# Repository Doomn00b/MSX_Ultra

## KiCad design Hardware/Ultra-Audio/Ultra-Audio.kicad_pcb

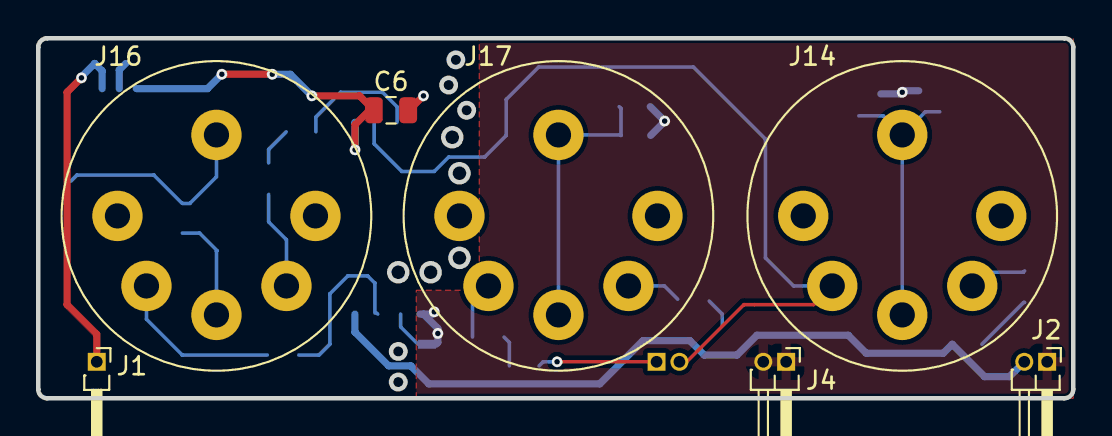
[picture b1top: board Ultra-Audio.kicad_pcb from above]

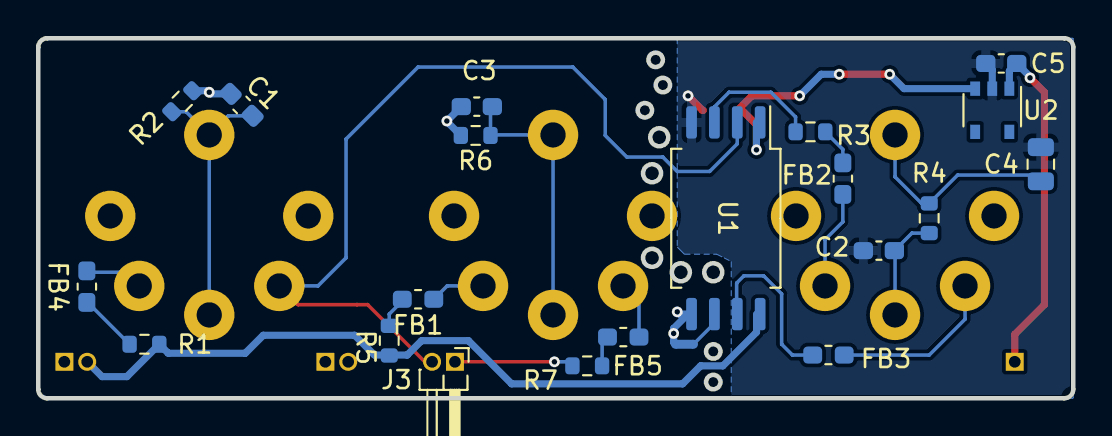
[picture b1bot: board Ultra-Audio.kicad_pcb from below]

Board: 2 copper layers, 57.5 x 20.0 mm, 28 parts (21 on the bottom side), 23 nets.

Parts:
C1, C2, C3, C5: C_CL10B104KB8NNNL; C_0603_1608Metric_Pad1.08x0.95mm_HandSolder
C4, C6: C_CL21B103KBANNNC; C_0805_2012Metric
FB1, FB2, FB3, FB4, FB5: L_ferrite_BLM18KG102SZ1D; L_0603_1608Metric_Pad1.05x0.95mm_HandSolder
J1: Conn_01x01; PinHeader_1x01_P1.27mm_Horizontal
J2, J3, J4: Conn_01x02; PinHeader_1x02_P1.27mm_Horizontal
J14, J16, J17: CUI_SD-50BV; Jack_DIN_CUI_SD-50BV_Vertical
R1, R3, R5, R7: R_CRGP0603F220R; R_0603_1608Metric
R2, R4, R6: R_ERJ-3GEYJ105V; R_0603_1608Metric
TP1: TestPoint_2Pole; NetTie-2_SMD_Pad0.5mm
U1: ADuM226; SOIC-8_7.5x5.85mm_P1.27mm
U2: AP7370; DIODES_SOT-753_SC-74A

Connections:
+5V: J2.2, R1.1, R5.1, U1.8 (VDD2)
+5VD: C6.1, U1.1 (VDD1), U2.3 (VOUT)
+12V: C5.1, J1.1, U2.1 (VIN)
/CSINKi: FB3.1, U1.7 (VIA)
/CSINKo: FB1.2, R5.2
/CSRCi: R3.1, U1.3 (VIB)
/CSRCo: FB5.1, R7.2
/MID_RX: J3.2, J14.5, U1.2 (VOA)
/MID_TX: J3.1, R7.1
Earth: C2.2, C4.2, C5.2, C6.2, U1.4 (GND1), U2.2 (GND)
GND: C1.2, C3.2, J2.1, J4.1, J4.2, R2.1, R6.1, TP1.1, U1.5 (GND2)
unnamed: C1.1, J14.2, J14.G, R2.2
unnamed: C2.1, J16.2, R4.1
unnamed: C3.1, J17.2, J17.G, R6.2
unnamed: C4.1, J16.G, R4.2
unnamed: FB1.1, J17.4
unnamed: FB2.1, J16.4
unnamed: FB2.2, R3.2
unnamed: FB3.2, J16.5
unnamed: FB4.1, J14.4
unnamed: FB4.2, R1.2
unnamed: FB5.2, J17.5
unnamed: TP1.2, U1.6 (VOB)

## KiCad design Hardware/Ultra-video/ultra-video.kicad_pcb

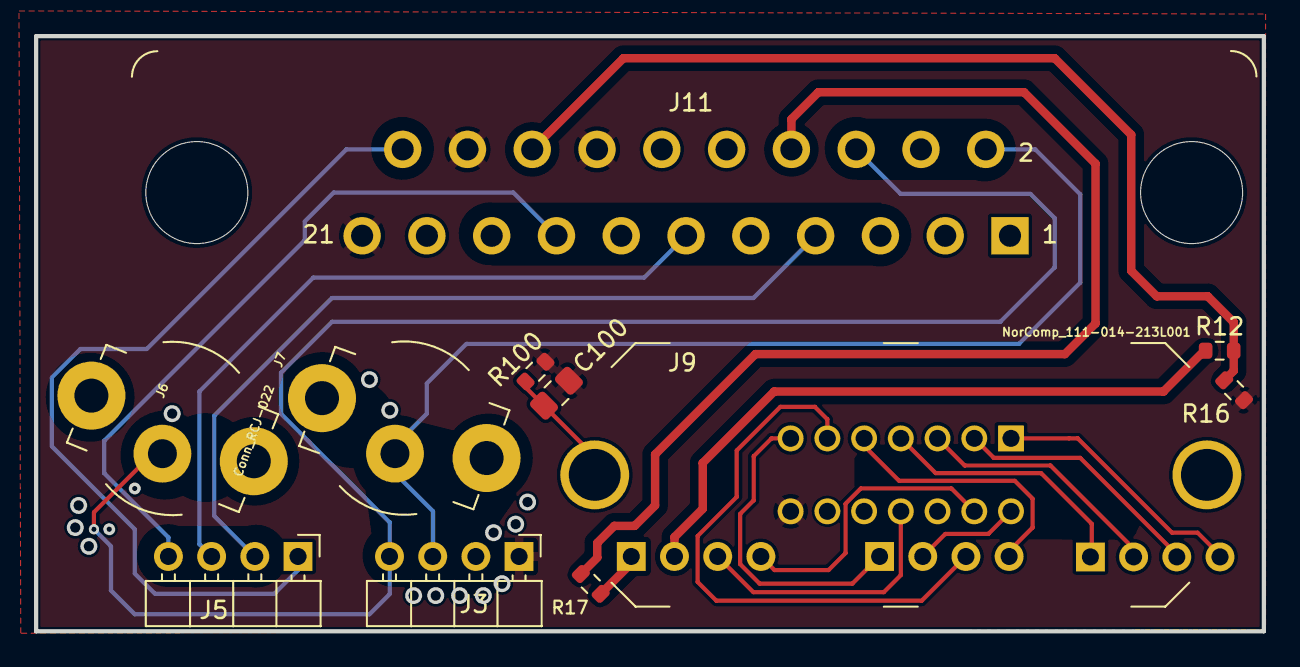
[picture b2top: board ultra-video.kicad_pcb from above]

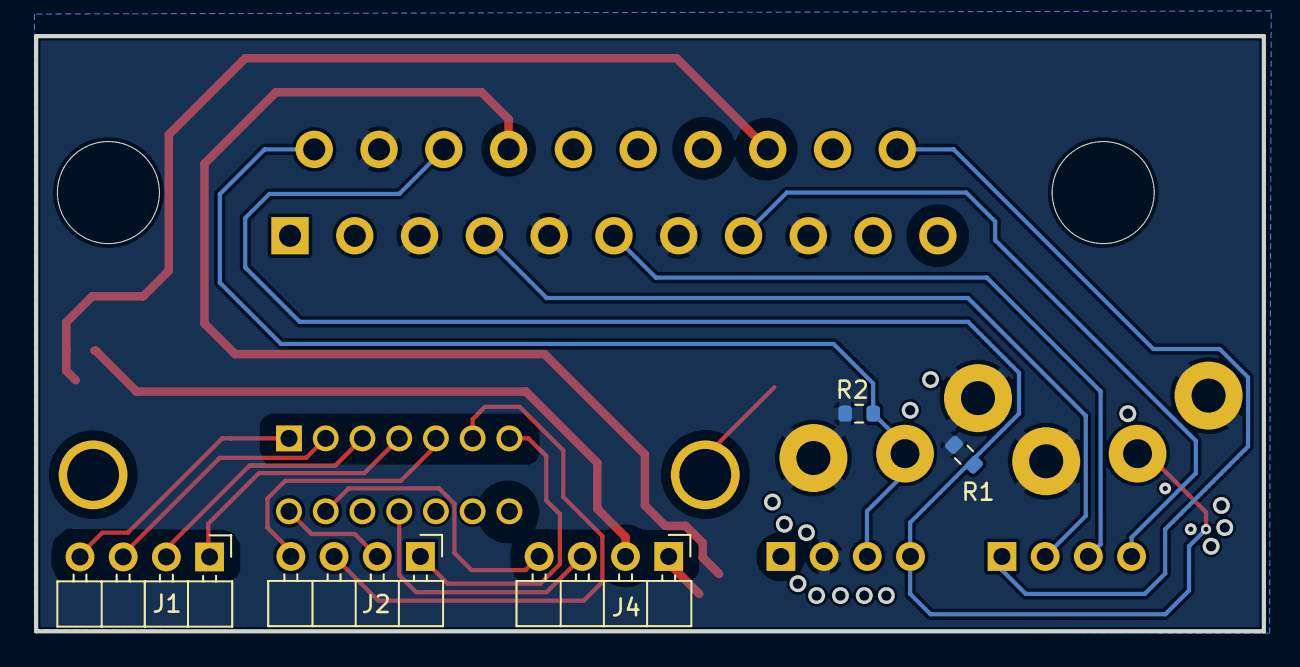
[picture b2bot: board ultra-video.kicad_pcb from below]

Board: 2 copper layers, 72.2 x 35.0 mm, 16 parts (5 on the bottom side), 23 nets.

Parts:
C100: C_CL21B105KBFNNNF; C_0805_2012Metric_Pad1.18x1.45mm_HandSolder
J1, J2, J3, J4, J5: Conn_01x04; PinHeader_1x04_P2.54mm_Horizontal_less-silk
J6: Conn_RCJ-023; CUI_RCJ-023
J7: Conn_RCJ-022; CUI_RCJ-022
J9: NorComp_111-014-213L001; Conn_Micro_Ribbon_14F_Vertical
J11: TC_1578891_SCART; SCART-21_Female_Vertical_P1.905x2.54mm_EdgePinOffset10.7mm
R1, R2: 47k; R_0603_1608Metric
R12, R16: 100; R_0603_1608Metric
R17: 1k; R_0603_1608Metric
R100: R_ERJ-3GEYJ105V; R_0603_1608Metric

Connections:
+5V: J4.2, R12.1
+12V: J4.1, R17.2
/2.5V: J11.16 (BLNK), R12.2, R16.1
/+12V-1K: J11.8 (SW), R17.1
/AUD_L: J3.4, J6.2 (IN2), J11.6 (AIL/MONO), R1.1
/AUD_R: J3.3, J7.2 (IN2), J11.2 (AIR), R2.2
/BOUT: J5.2, J11.7 (BLUE)
/CSYNC: J5.1, J11.20 (VIDIN/Sync)
/GOUT: J5.3, J11.11 (GREEN)
/PD0: J1.3, J9.2
/PD1: J1.2, J9.3
/PD2: J1.1, J9.4
/PD3: J2.4, J9.5
/PD4: J2.3, J9.6
/PD5: J2.1, J9.7
/PD6: J2.2, J9.8
/PD7: J4.4, J9.9
/PRT_BUSY: J4.3, J9.11
/ROUT: J5.4, J11.15 (RED/CHROMA)
/~STROBE: J1.4, J9.1
GND: C100.2, J3.1, J9.14, J11.14 (DATGND), J11.18 (BLNKGND), J11.21 (SH), R16.2, R100.1
GNDA: J3.2, J6.1A (IN1), J6.1B (IN1), J7.1A (IN1), J7.1B (IN1), J11.4 (AUGND), J11.5 (BGND), J11.9 (GGND), J11.13 (RGND), J11.17 (VGND), R1.2, R2.1
unnamed: C100.1, J9.15 (SH), R100.2

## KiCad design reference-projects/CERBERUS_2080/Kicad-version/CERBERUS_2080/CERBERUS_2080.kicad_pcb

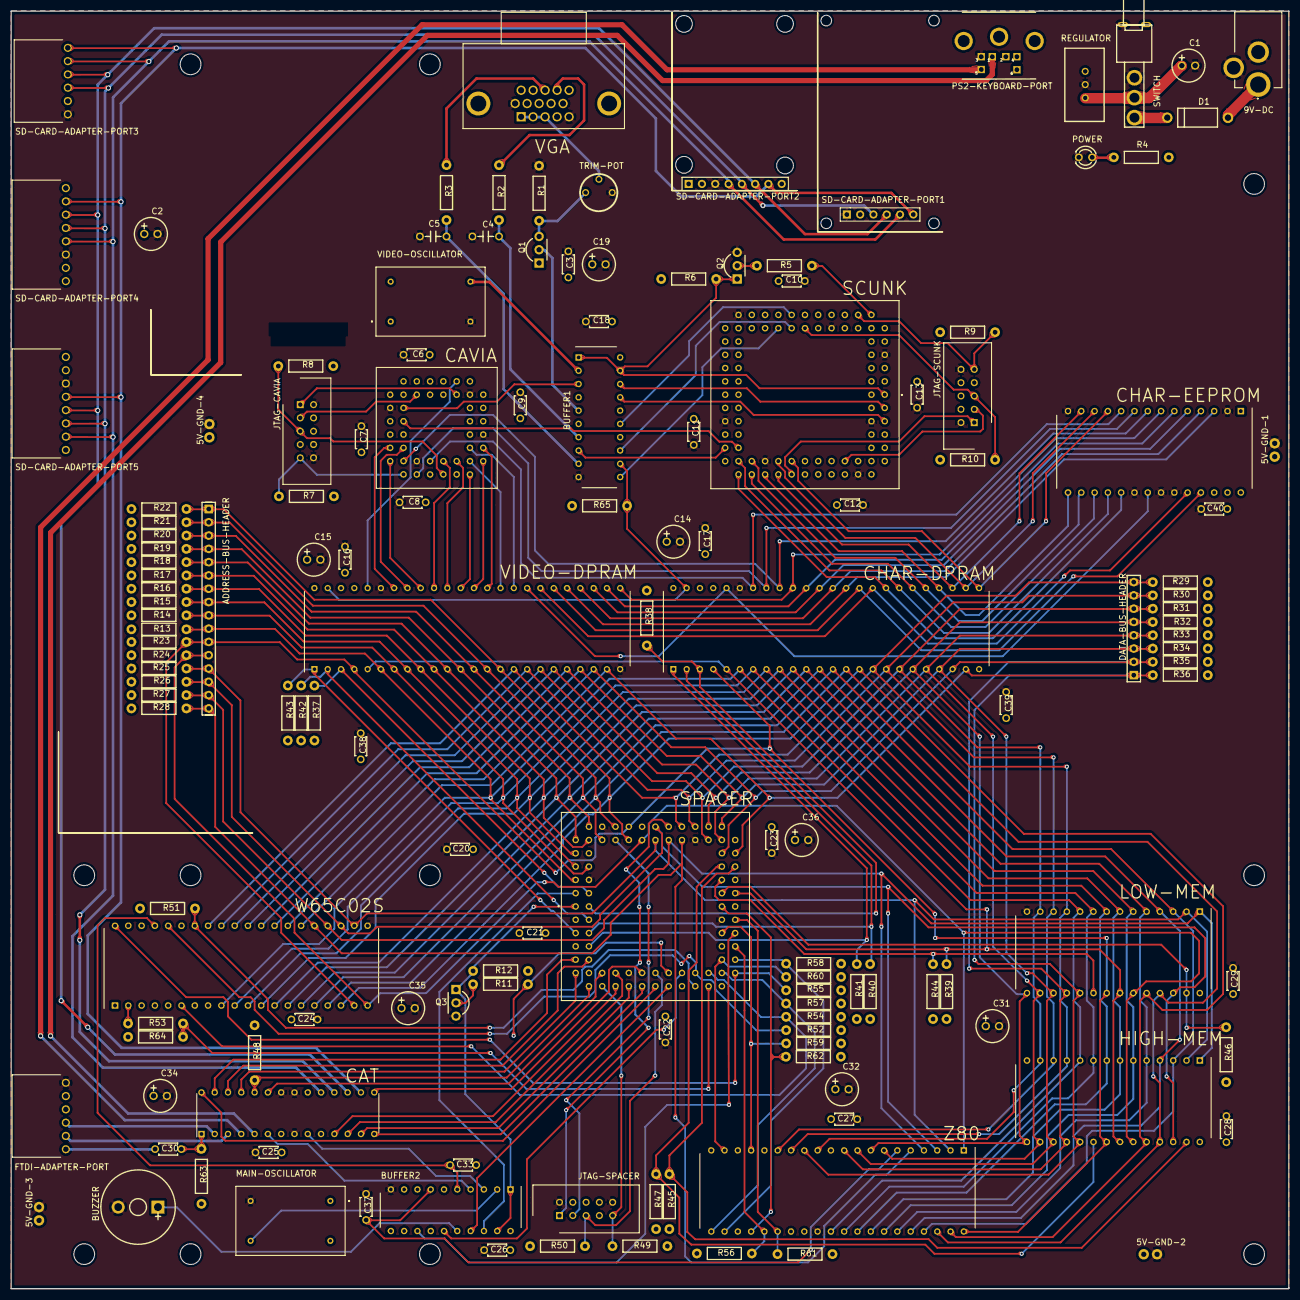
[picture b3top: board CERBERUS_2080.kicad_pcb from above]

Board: 2 copper layers, 244.1 x 244.1 mm, 147 parts (0 on the bottom side), 150 nets.

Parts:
5V-GND-1, 5V-GND-2, 5V-GND-3, 5V-GND-4: Pin Header, VERT, TH, 2.54mm; HDR-TH_2P-P2.54-V-R1-C2-D1.0
9V-DC: Wurth-Elektronik-694106301002; KLDX0202APLT
ADDRESS-BUS-HEADER: P125-1116A0BS116AX; H16-2.54
BUFFER1, BUFFER2: SN74HC244N; DIP794W53P254L2540H508Q20N
BUZZER: Ekulit RMP-14SP; BUZZER-R14-2P-7.6PITCH
C1: 470µF; CAP-TH_BD6.3-P2.50-D1.0-FD
C2, C19, C31, C35: 10µF; CAP-TH_BD6.3-P2.50-D1.0-FD
C3, C6, C7, C8, C9, C10, C11, C12, C13, C16, C17, C18, C20, C21, C22, C23, C24, C25, C26, C27, C28, C29, C30, C38, C39, C40: 100nF; CAP-TH_L3.6-W2.3-P5.00-D0.5
C4, C5: 470pF; CAP-TH_L5.0-W2.5-P5.08-D0.7
C14, C15, C32, C34, C36: 100µF; CAP-TH_BD6.3-P2.50-D1.0-FD
C33, C37: 100pF; CAP-TH_L3.6-W2.3-P5.00-D0.5
CAT: ATMEGA328P-PU; DIP794W53P254L3467H457Q28N
CAVIA: ATF1504AS; PLCC-44
CHAR-DPRAM: 7132LA55PDGI; DIP1549W51P254L6185H508Q48N
CHAR-EEPROM: AT28C64B-15PU; DIP1556W56P254L3702H483Q28N
D1: SB2H100-E3/54; DO-15_BD3.1-L6.7-P10.70-D0.9-RD
DATA-BUS-HEADER: F185-1108A1BSYC1; H8-2.54
FTDI-ADAPTER-PORT: SSW-106-02-F-S-RA; SSW-106-XX-YYY-S-RA
HIGH-MEM: AS6C62256-55PCN; DIP1556W56P254L3702H483Q28N
JTAG-CAVIA: 103308-1; SHDR10W66P254_2X5_2032X914X978
JTAG-SCUNK: 103308-1; SHDR10W66P254_2X5_2032X914X978
JTAG-SPACER: 103308-1; SHDR10W66P254_2X5_2032X914X978
LOW-MEM: AS6C62256-55PCN; DIP1556W56P254L3702H483Q28N
MAIN-OSCILLATOR: OSZI 16,000000; ECS100AX240
POWER: Wurth-Elektronik-151051BS04000; LED-TH_BD3.0-P2.54-FD
PS2-KEYBOARD-PORT: CADANIA 1AA300833_JHJC; PS2_PORT
Q1: BC337-40; TO-92-3_L4.8-W3.7-P2.54-L
Q2, Q3: BC547B; TO-92-3_L4.8-W3.7-P2.54-L
R1, R4: 220Ω; RES-TH_BD2.3-L6.5-P10.50-D0.5
R2, R3: 68Ω; RES-TH_BD2.3-L6.5-P10.50-D0.5
R5, R6, R7, R8, R9, R10, R11, R12, R13, R14, R15, R16, R17, R18, R19, R20, R21, R22, R23, R24, R25, R26, R27, R28, R29, R30, R31, R32, R33, R34, R35, R36, R39, R40, R41, R42, R43, R44, R45, R46, R47, R48, R49, R50, R51, R52, R54, R55, R56, R57, R58, R59, R60, R61, R62, R63, R64, R65: 10KΩ; RES-TH_BD2.3-L6.5-P10.50-D0.5
R37, R38: 270Ω; RES-TH_BD2.3-L6.5-P10.50-D0.5
R53: 2K2Ω; RES-TH_BD2.3-L6.5-P10.50-D0.5
REGULATOR: TSR_2-2450; TSR-2
SCUNK: ATF1508AS; 5408808424008
SD-CARD-ADAPTER-PORT1: MOLEX 90147-1106; HDR-F-2.54_1X6
SD-CARD-ADAPTER-PORT2: MOLEX 90147-1108; HDR-F-2.54_1X8
SD-CARD-ADAPTER-PORT3: SSW-106-02-F-S-RA; SSW-106-XX-YYY-S-RA
SD-CARD-ADAPTER-PORT4, SD-CARD-ADAPTER-PORT5: SSW-108-02-G-S-RA; SSW-108-XX-YYY-S-RA
SPACER: ATF1508AS; 5408808424008
SWITCH: 500SSP1S2M7QEA; SW-TH_500SSP1S2M7QEA
TRIM-POT: T7YA103MT20; T7YA
VGA: L77HDE15SD1CH4RHNVGA
VIDEO-DPRAM: 7132LA55PDGI; DIP1549W51P254L6185H508Q48N
VIDEO-OSCILLATOR: ECS-100AX-25.175; ECS100AX240
W65C02S: W65C02S6TPG-14; DIP1524W56P254L5207H508Q40N
Z80: Z84C0010PEG; DIP1550W53P254L5232H424Q40N

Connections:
9V-DC_1: 9V-DC.1, D1.2
A0: ADDRESS-BUS-HEADER.10, CHAR-DPRAM.6, HIGH-MEM.10, LOW-MEM.10, R13.2, SPACER.81, VIDEO-DPRAM.6, W65C02S.9, Z80.30
A1: ADDRESS-BUS-HEADER.9, CHAR-DPRAM.7, HIGH-MEM.9, LOW-MEM.9, R14.2, SPACER.80, VIDEO-DPRAM.7, W65C02S.10, Z80.31
A2: ADDRESS-BUS-HEADER.8, CHAR-DPRAM.8, HIGH-MEM.8, LOW-MEM.8, R15.2, SPACER.79, VIDEO-DPRAM.8, W65C02S.11, Z80.32
A3: ADDRESS-BUS-HEADER.7, CHAR-DPRAM.9, HIGH-MEM.7, LOW-MEM.7, R16.2, SPACER.77, VIDEO-DPRAM.9, W65C02S.12, Z80.33
A4: ADDRESS-BUS-HEADER.6, CHAR-DPRAM.10, HIGH-MEM.6, LOW-MEM.6, R17.2, SPACER.76, VIDEO-DPRAM.10, W65C02S.13, Z80.34
A5: ADDRESS-BUS-HEADER.5, CHAR-DPRAM.11, HIGH-MEM.5, LOW-MEM.5, R18.2, SPACER.75, VIDEO-DPRAM.11, W65C02S.14, Z80.35
A6: ADDRESS-BUS-HEADER.4, CHAR-DPRAM.12, HIGH-MEM.4, LOW-MEM.4, R19.2, SPACER.74, VIDEO-DPRAM.12, W65C02S.15, Z80.36
A7: ADDRESS-BUS-HEADER.3, CHAR-DPRAM.13, HIGH-MEM.3, LOW-MEM.3, R20.2, SPACER.73, VIDEO-DPRAM.13, W65C02S.16, Z80.37
A8: ADDRESS-BUS-HEADER.2, CHAR-DPRAM.14, HIGH-MEM.25, LOW-MEM.25, R21.2, SPACER.70, VIDEO-DPRAM.14, W65C02S.17, Z80.38
A9: ADDRESS-BUS-HEADER.1, CHAR-DPRAM.15, HIGH-MEM.24, LOW-MEM.24, R22.2, SPACER.69, VIDEO-DPRAM.15, W65C02S.18, Z80.39
A10: ADDRESS-BUS-HEADER.11, CHAR-DPRAM.4, HIGH-MEM.21, LOW-MEM.21, R23.2, SPACER.68, VIDEO-DPRAM.4, W65C02S.19, Z80.40
A11: ADDRESS-BUS-HEADER.12, HIGH-MEM.23, LOW-MEM.23, R24.2, SPACER.67, W65C02S.20, Z80.1
A12: ADDRESS-BUS-HEADER.13, HIGH-MEM.2, LOW-MEM.2, R25.2, SPACER.65, W65C02S.22, Z80.2
A13: ADDRESS-BUS-HEADER.14, HIGH-MEM.26, LOW-MEM.26, R26.2, SPACER.64, W65C02S.23, Z80.3
A14: ADDRESS-BUS-HEADER.15, HIGH-MEM.1, LOW-MEM.1, R27.2, SPACER.63, W65C02S.24, Z80.4
A15: ADDRESS-BUS-HEADER.16, R28.2, SPACER.61, W65C02S.25, Z80.5
AOE: CAT.25, SPACER.11
BCATCLK: BUFFER2.3, CAT.9
BCCLK: BUFFER1.3, CAVIA.43
BCLK6502: BUFFER2.5, C33.2, W65C02S.37
BCLKZ80: BUFFER2.7, C37.2, Z80.6
BDPMCE: BUFFER1.12, CHAR-DPRAM.47, R65.1, VIDEO-DPRAM.47
BE6502: R52.2, SPACER.29, W65C02S.36
BMCLK: BUFFER2.18, SPACER.83
BPCLK: BUFFER1.18, SCUNK.83
BSOUND: BUFFER2.16, BUZZER.1
BUFFER1_5: BUFFER1.5, Q1.2
BUFFER1_7: BUFFER1.7, C4.1, R2.1
BUFFER1_9: BUFFER1.9, C5.1, R3.1
BUSREQZ80: R56.2, SPACER.37, Z80.25
C1_1: C1.1, REGULATOR.1, SWITCH.2
C-TCK: CAVIA.32, JTAG-CAVIA.1
C-TDI: CAVIA.7, JTAG-CAVIA.9, R7.1
C-TDO: CAVIA.38, JTAG-CAVIA.3
C-TMS: CAVIA.13, JTAG-CAVIA.5, R8.1
CATCLK: BUFFER2.17, SPACER.24
CATEXTRA: CAT.15, SPACER.21
CATRST: C30.1, FTDI-ADAPTER-PORT.6
CAT_1: C30.2, CAT.1, R63.2
CB0: CHAR-DPRAM.25, CHAR-EEPROM.11, SCUNK.63
CB1: CHAR-DPRAM.26, CHAR-EEPROM.12, SCUNK.61
CB2: CHAR-DPRAM.27, CHAR-EEPROM.13, SCUNK.60
CB3: CHAR-DPRAM.28, CHAR-EEPROM.15, SCUNK.58
CB4: CHAR-DPRAM.29, CHAR-EEPROM.16, SCUNK.57
CB5: CHAR-DPRAM.30, CHAR-EEPROM.17, SCUNK.56
CB6: CHAR-DPRAM.31, CHAR-EEPROM.18, SCUNK.55
CB7: CHAR-DPRAM.32, CHAR-EEPROM.19, SCUNK.54
CBUSY: CHAR-DPRAM.3, R38.2, SPACER.2
CCLK: BUFFER1.17, SCUNK.81
CECM: CHAR-DPRAM.1, R41.2, SPACER.8
CEHM: HIGH-MEM.20, R47.2, SPACER.50
CELM: LOW-MEM.20, R44.2, SPACER.48
CEVM: R43.2, SPACER.5, VIDEO-DPRAM.1
CLK6502: BUFFER2.15, SPACER.27
CLKZ80: BUFFER2.13, SPACER.39
CMA0: CAVIA.12, CHAR-DPRAM.42, CHAR-EEPROM.10
CMA1: CAVIA.9, CHAR-DPRAM.41, CHAR-EEPROM.9
CMA2: CAVIA.8, CHAR-DPRAM.40, CHAR-EEPROM.8
CMA3: CHAR-DPRAM.39, CHAR-EEPROM.7, VIDEO-DPRAM.25
CMA4: CHAR-DPRAM.38, CHAR-EEPROM.6, VIDEO-DPRAM.26
CMA5: CHAR-DPRAM.37, CHAR-EEPROM.5, VIDEO-DPRAM.27
CMA6: CHAR-DPRAM.36, CHAR-EEPROM.4, VIDEO-DPRAM.28
CMA7: CHAR-DPRAM.35, CHAR-EEPROM.3, VIDEO-DPRAM.29
CMA8: CHAR-DPRAM.34, CHAR-EEPROM.25, VIDEO-DPRAM.30
CMA9: CHAR-DPRAM.33, CHAR-EEPROM.24, VIDEO-DPRAM.31
CMA10: CHAR-DPRAM.44, CHAR-EEPROM.21, VIDEO-DPRAM.32
CPUGO: CAT.13, SPACER.18
CPUIRQ: CAT.12, SPACER.17
CPURST: CAT.14, SPACER.20
CPUSLC: CAT.11, SPACER.16
CRST: CAVIA.1, SCUNK.52
CS: CAT.16, SD-CARD-ADAPTER-PORT1.6, SD-CARD-ADAPTER-PORT2.7, SD-CARD-ADAPTER-PORT3.1, SD-CARD-ADAPTER-PORT4.2, SD-CARD-ADAPTER-PORT5.4
D0: CHAR-DPRAM.16, DATA-BUS-HEADER.8, HIGH-MEM.11, LOW-MEM.11, R29.2, SPACER.60, VIDEO-DPRAM.16, W65C02S.33, Z80.14
D1: CHAR-DPRAM.17, DATA-BUS-HEADER.7, HIGH-MEM.12, LOW-MEM.12, R30.2, SPACER.58, VIDEO-DPRAM.17, W65C02S.32, Z80.15
D1_1: D1.1, SWITCH.3
D2: CHAR-DPRAM.18, DATA-BUS-HEADER.6, HIGH-MEM.13, LOW-MEM.13, R31.2, SPACER.57, VIDEO-DPRAM.18, W65C02S.31, Z80.12
D3: CHAR-DPRAM.19, DATA-BUS-HEADER.5, HIGH-MEM.15, LOW-MEM.15, R32.2, SPACER.56, VIDEO-DPRAM.19, W65C02S.30, Z80.8
D4: CHAR-DPRAM.20, DATA-BUS-HEADER.4, HIGH-MEM.16, LOW-MEM.16, R33.2, SPACER.55, VIDEO-DPRAM.20, W65C02S.29, Z80.7
D5: CHAR-DPRAM.21, DATA-BUS-HEADER.3, HIGH-MEM.17, LOW-MEM.17, R34.2, SPACER.54, VIDEO-DPRAM.21, W65C02S.28, Z80.9
D6: CHAR-DPRAM.22, DATA-BUS-HEADER.2, HIGH-MEM.18, LOW-MEM.18, R35.2, SPACER.52, VIDEO-DPRAM.22, W65C02S.27, Z80.10
D7: CHAR-DPRAM.23, DATA-BUS-HEADER.1, HIGH-MEM.19, LOW-MEM.19, R36.2, SPACER.51, VIDEO-DPRAM.23, W65C02S.26, Z80.13
DPMCE: BUFFER1.8, SCUNK.51
GND: 5V-GND-1.1, 5V-GND-2.1, 5V-GND-3.1, 5V-GND-4.1, 9V-DC.2, 9V-DC.3, BUFFER1.10, BUFFER2.10, BUZZER.2, C1.2, C2.2, C3.2, C4.2, C5.2, C6.2, C7.2, C8.2, C9.2, C10.2, C11.2, C12.2, C13.2, C14.2, C15.2, C16.2, C17.2, C18.2, C19.2, C20.2, C21.2, C22.2, C23.2, C24.2, C25.2, C26.2, C27.2, C28.2, C29.2, C31.2, C32.2, C33.1, C34.2, C35.2, C36.2, C37.1, C38.2, C39.2, C40.2, CAT.8, CAT.21, CAT.22, CAVIA.10, CAVIA.22, CAVIA.30, CAVIA.42, CHAR-DPRAM.24, CHAR-DPRAM.43, CHAR-EEPROM.2, CHAR-EEPROM.14, CHAR-EEPROM.20, CHAR-EEPROM.22, CHAR-EEPROM.23, FTDI-ADAPTER-PORT.1, HIGH-MEM.14, JTAG-CAVIA.2, JTAG-CAVIA.10, JTAG-SCUNK.2, JTAG-SCUNK.10, JTAG-SPACER.2, JTAG-SPACER.10, LOW-MEM.14, MAIN-OSCILLATOR.7, POWER.2, PS2-KEYBOARD-PORT.3, Q2.3, Q3.3, R1.1, REGULATOR.2, SCUNK.7, SCUNK.19, SCUNK.32, SCUNK.42, SCUNK.47, SCUNK.59, SCUNK.72, SCUNK.82, SD-CARD-ADAPTER-PORT1.1, SD-CARD-ADAPTER-PORT2.3, SD-CARD-ADAPTER-PORT3.6, SD-CARD-ADAPTER-PORT4.6, SD-CARD-ADAPTER-PORT5.3, SPACER.7, SPACER.19, SPACER.32, SPACER.42, SPACER.47, SPACER.59, SPACER.72, SPACER.82, SWITCH.1, SWITCH.5, TRIM-POT.C, VGA.5, VGA.6, VGA.7, VGA.8, VGA.10, VIDEO-DPRAM.24, VIDEO-DPRAM.43, VIDEO-OSCILLATOR.7, W65C02S.21, Z80.29
HSP: BUFFER1.11, SCUNK.27
KCLK: CAT.4, PS2-KEYBOARD-PORT.5
KDAT: CAT.5, PS2-KEYBOARD-PORT.1
LD: CAT.23, SPACER.15
MCLK: BUFFER2.2, MAIN-OSCILLATOR.8
MISO: CAT.18, SD-CARD-ADAPTER-PORT1.3, SD-CARD-ADAPTER-PORT2.5, SD-CARD-ADAPTER-PORT3.4, SD-CARD-ADAPTER-PORT4.4, SD-CARD-ADAPTER-PORT5.6
MOSI: CAT.17, SD-CARD-ADAPTER-PORT1.4, SD-CARD-ADAPTER-PORT2.6, SD-CARD-ADAPTER-PORT3.3, SD-CARD-ADAPTER-PORT4.3, SD-CARD-ADAPTER-PORT5.5
MREQZ80: R60.2, SPACER.36, Z80.19
NMIB6502: R54.2, SPACER.31, W65C02S.6
NMIZ80: R59.2, SPACER.40, Z80.17
OE: CHAR-DPRAM.5, HIGH-MEM.22, LOW-MEM.22, R39.2, SPACER.45, VIDEO-DPRAM.5
PCLK: BUFFER1.2, VIDEO-OSCILLATOR.8
POWER_1: POWER.1, R4.2
Q2_2: Q2.2, R5.1
R11_1: Q3.2, R11.1
RDY6502: R53.1, R64.2, SPACER.30
RDZ80: R57.2, SPACER.34, Z80.21
RGB: BUFFER1.15, SCUNK.24
RST6502: R55.2, SPACER.33, W65C02S.40
RSTZ80: R61.2, SPACER.41, Z80.26
RWB6502: R51.2, SPACER.28, W65C02S.34
RWCAT: CAT.24, R48.2, SPACER.12
RWCM: CHAR-DPRAM.2, R40.2, SPACER.6
RWVM: R42.2, SPACER.4, VIDEO-DPRAM.2
RX: CAT.2, FTDI-ADAPTER-PORT.4
S-TCK: JTAG-SCUNK.1, SCUNK.62
S-TDI: JTAG-SCUNK.9, R9.1, SCUNK.14
S-TDO: JTAG-SCUNK.3, SCUNK.71
S-TMS: JTAG-SCUNK.5, R10.1, SCUNK.23
SBE: R5.2, SCUNK.12
SC: CAT.26, SPACER.10
SCK: CAT.19, SD-CARD-ADAPTER-PORT1.5, SD-CARD-ADAPTER-PORT2.4, SD-CARD-ADAPTER-PORT3.2, SD-CARD-ADAPTER-PORT4.5, SD-CARD-ADAPTER-PORT5.7
SI: CAT.27, SPACER.9
SO: CAT.28, SPACER.22
SOUND: BUFFER2.4, CAT.6
SP-TCK: JTAG-SPACER.1, SPACER.62
SP-TDI: JTAG-SPACER.9, R49.1, SPACER.14
SP-TDO: JTAG-SPACER.3, SPACER.71
SP-TMS: JTAG-SPACER.5, R50.1, SPACER.23
SPBE: R11.2, SPACER.25
SPRST: BUFFER2.1, BUFFER2.19, Q3.1, R12.1, SPACER.1
SRST: BUFFER1.1, BUFFER1.19, Q2.1, R6.1, SCUNK.1
TRIM-POT_A: Q1.3, R1.2, TRIM-POT.A
TX: CAT.3, FTDI-ADAPTER-PORT.5
VBUSY: R37.2, SPACER.84, VIDEO-DPRAM.3
VCC: 5V-GND-1.2, 5V-GND-2.2, 5V-GND-3.2, 5V-GND-4.2, BUFFER1.20, BUFFER2.20, C2.1, C3.1, C6.1, C7.1, C8.1, C9.1, C10.1, C11.1, C12.1, C13.1, C14.1, C15.1, C16.1, C17.1, C18.1, C19.1, C20.1, C21.1, C22.1, C23.1, C24.1, C25.1, C26.1, C27.1, C28.1, C29.1, C31.1, C32.1, C34.1, C35.1, C36.1, C38.1, C39.1, C40.1, CAT.7, CAT.20, CAVIA.3, CAVIA.15, CAVIA.23, CAVIA.35, CHAR-DPRAM.46, CHAR-DPRAM.48, CHAR-EEPROM.27, CHAR-EEPROM.28, FTDI-ADAPTER-PORT.3, HIGH-MEM.28, JTAG-CAVIA.4, JTAG-SCUNK.4, JTAG-SPACER.4, LOW-MEM.28, MAIN-OSCILLATOR.14, PS2-KEYBOARD-PORT.4, Q1.1, R4.1, R6.2, R7.2, R8.2, R9.2, R10.2, R12.2, R13.1, R14.1, R15.1, R16.1, R17.1, R18.1, R19.1, R20.1, R21.1, R22.1, R23.1, R24.1, R25.1, R26.1, R27.1, R28.1, R29.1, R30.1, R31.1, R32.1, R33.1, R34.1, R35.1, R36.1, R37.1, R38.1, R39.1, R40.1, R41.1, R42.1, R43.1, R44.1, R45.1, R46.1, R47.1, R48.1, R49.2, R50.2, R51.1, R52.1, R54.1, R55.1, R56.1, R57.1, R58.1, R59.1, R60.1, R61.1, R62.1, R63.1, R64.1, R65.2, REGULATOR.3, SCUNK.3, SCUNK.13, SCUNK.26, SCUNK.38, SCUNK.43, SCUNK.53, SCUNK.66, SCUNK.78, SD-CARD-ADAPTER-PORT1.2, SD-CARD-ADAPTER-PORT2.1, SD-CARD-ADAPTER-PORT3.5, SD-CARD-ADAPTER-PORT4.8, SD-CARD-ADAPTER-PORT5.1, SPACER.3, SPACER.13, SPACER.26, SPACER.38, SPACER.43, SPACER.53, SPACER.66, SPACER.78, VIDEO-DPRAM.46, VIDEO-DPRAM.48, VIDEO-OSCILLATOR.14, W65C02S.4, W65C02S.8, W65C02S.38, Z80.11, Z80.16
VGA_1: TRIM-POT.B, VGA.1, VGA.2, VGA.3
VGA_13: R3.2, VGA.13
VGA_14: R2.2, VGA.14
VMA0: CAVIA.4, VIDEO-DPRAM.42
VMA1: CAVIA.5, VIDEO-DPRAM.41
VMA2: CAVIA.6, VIDEO-DPRAM.40
VMA3: CAVIA.14, VIDEO-DPRAM.39
VMA4: CAVIA.16, VIDEO-DPRAM.38
VMA5: CAVIA.17, VIDEO-DPRAM.37
VMA6: CAVIA.18, VIDEO-DPRAM.36
VMA7: CAVIA.20, VIDEO-DPRAM.35
VMA8: CAVIA.19, VIDEO-DPRAM.34
VMA9: CAVIA.21, VIDEO-DPRAM.33
VMA10: CAVIA.31, VIDEO-DPRAM.44
VSP: BUFFER1.13, SCUNK.25
W65C02S_2: R53.2, W65C02S.2
WAITZ80: R62.2, SPACER.44, Z80.24
WEHM: HIGH-MEM.27, R45.2, SPACER.49
WELM: LOW-MEM.27, R46.2, SPACER.46
WRZ80: R58.2, SPACER.35, Z80.22

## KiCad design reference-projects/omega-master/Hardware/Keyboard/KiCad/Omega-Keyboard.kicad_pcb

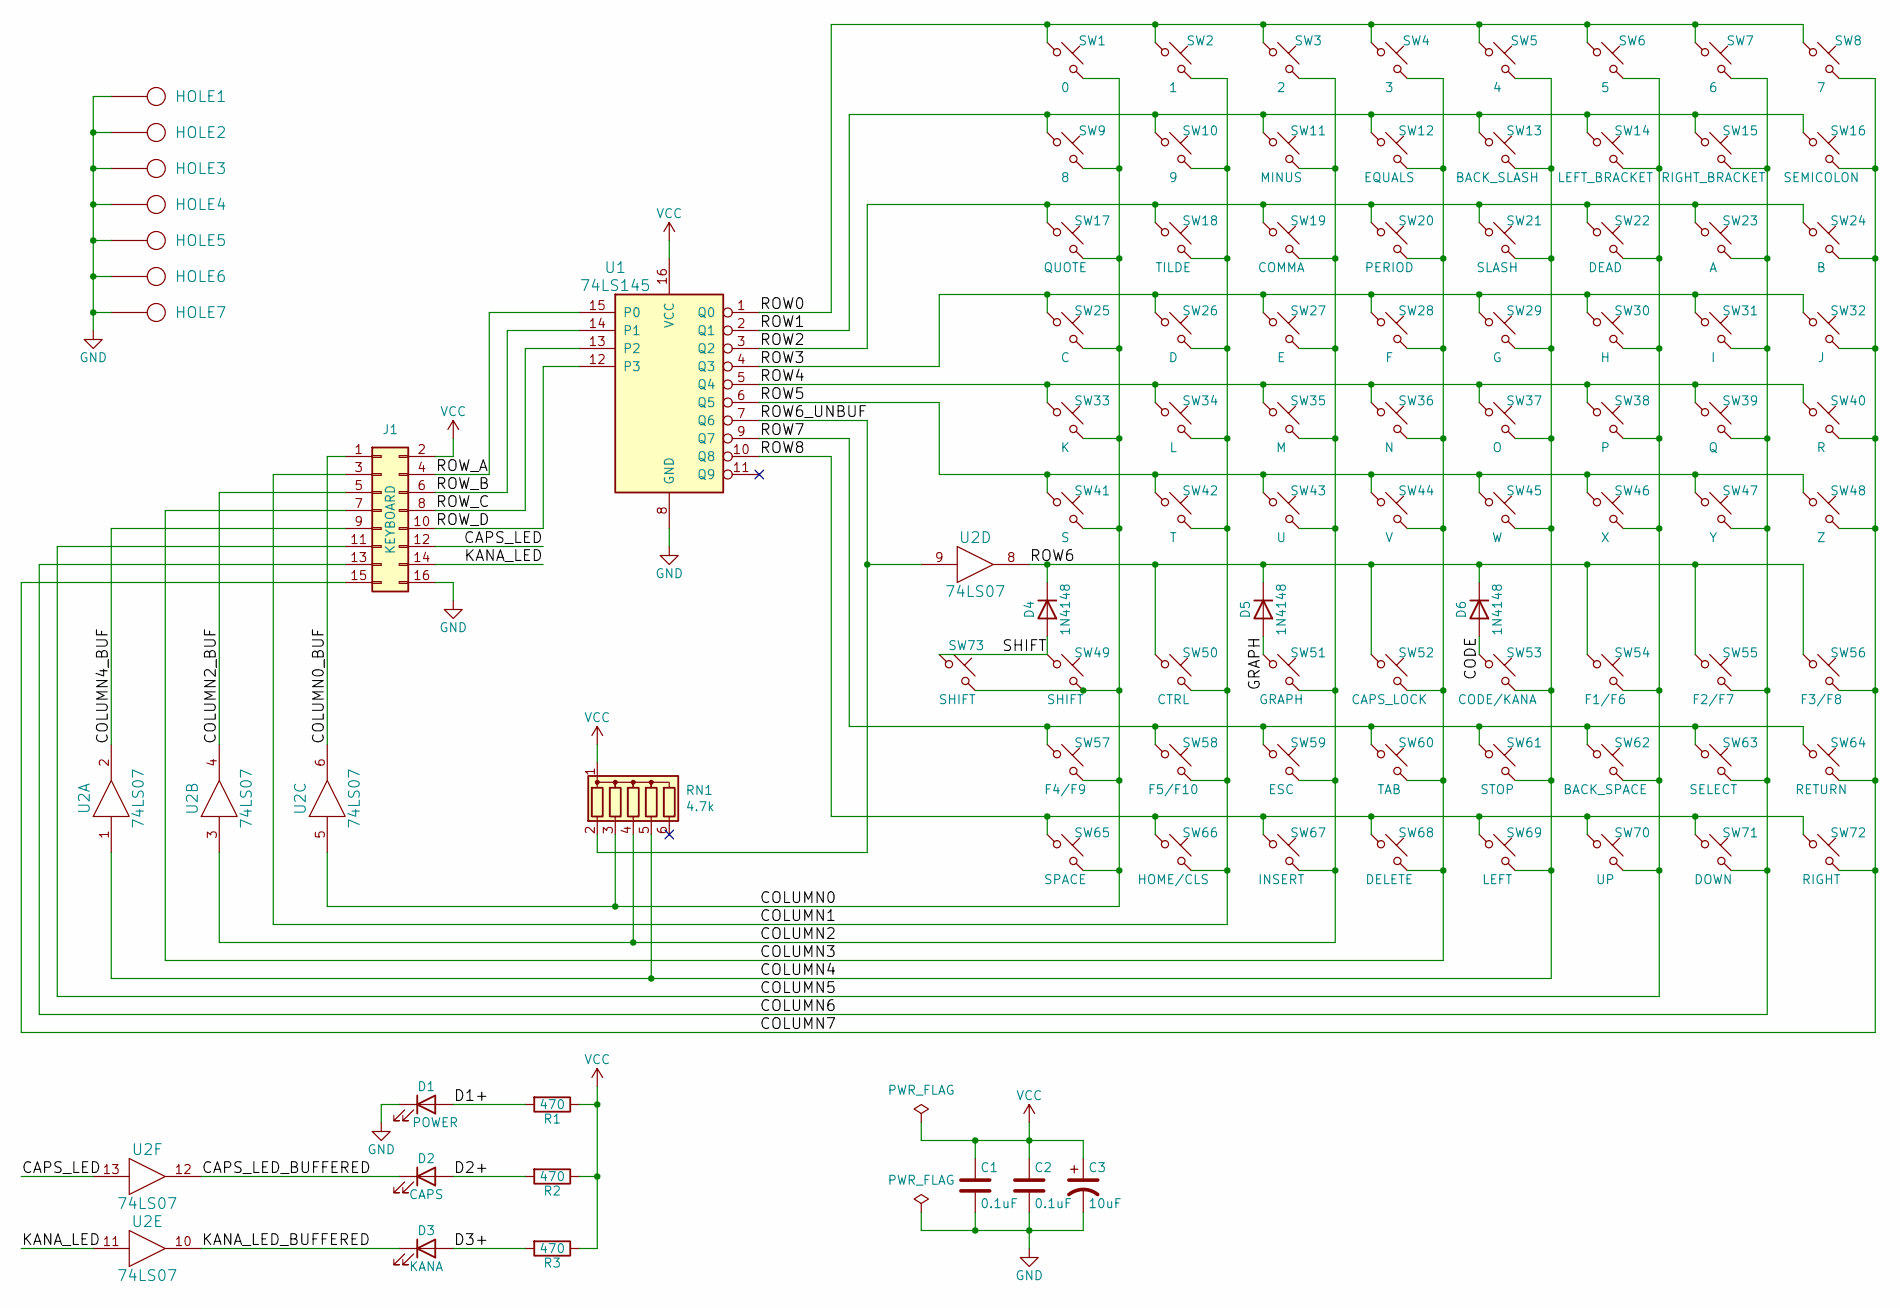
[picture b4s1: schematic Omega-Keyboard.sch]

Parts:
C1, C2: 0.1uF; Cap_Cer_508
C3: 10uF; Cap_Tant_508
D1: POWER; LED_3mm
D2: CAPS; CHERRY_MX_LED
D3: KANA; CHERRY_MX_LED
D4, D5, D6: 1N4148; Diode_762
HOLE1, HOLE2, HOLE3, HOLE4, HOLE5, HOLE6, HOLE7: HOLE; Hole_3mm
J1: KEYBOARD; Conn_Pin_Header_8x2_2.54mm
R1, R2, R3: 470; Res_762
RN1: 4.7k; Conn_SIL6
SW1: 0; CHERRY_PCB_100H
SW2: 1; CHERRY_PCB_100H
SW3: 2; CHERRY_PCB_100H
SW4: 3; CHERRY_PCB_100H
SW5: 4; CHERRY_PCB_100H
SW6: 5; CHERRY_PCB_100H
SW7: 6; CHERRY_PCB_100H
SW8: 7; CHERRY_PCB_100H
SW9: 8; CHERRY_PCB_100H
SW10: 9; CHERRY_PCB_100H
SW11: MINUS; CHERRY_PCB_100H
SW12: EQUALS; CHERRY_PCB_100H
SW13: BACK_SLASH; CHERRY_PCB_150H
SW14: LEFT_BRACKET; CHERRY_PCB_100H
SW15: RIGHT_BRACKET; CHERRY_PCB_100H
SW16: SEMICOLON; CHERRY_PCB_100H
SW17: QUOTE; CHERRY_PCB_100H
SW18: TILDE; CHERRY_PCB_100H
SW19: COMMA; CHERRY_PCB_100H
SW20: PERIOD; CHERRY_PCB_100H
SW21: SLASH; CHERRY_PCB_100H
SW22: DEAD; CHERRY_PCB_125H
SW23: A; CHERRY_PCB_100H
SW24: B; CHERRY_PCB_100H
SW25: C; CHERRY_PCB_100H
SW26: D; CHERRY_PCB_100H
SW27: E; CHERRY_PCB_100H
SW28: F; CHERRY_PCB_100H
SW29: G; CHERRY_PCB_100H
SW30: H; CHERRY_PCB_100H
SW31: I; CHERRY_PCB_100H
SW32: J; CHERRY_PCB_100H
SW33: K; CHERRY_PCB_100H
SW34: L; CHERRY_PCB_100H
SW35: M; CHERRY_PCB_100H
SW36: N; CHERRY_PCB_100H
SW37: O; CHERRY_PCB_100H
SW38: P; CHERRY_PCB_100H
SW39: Q; CHERRY_PCB_100H
SW40: R; CHERRY_PCB_100H
SW41: S; CHERRY_PCB_100H
SW42: T; CHERRY_PCB_100H
SW43: U; CHERRY_PCB_100H
SW44: V; CHERRY_PCB_100H
SW45: W; CHERRY_PCB_100H
SW46: X; CHERRY_PCB_100H
SW47: Y; CHERRY_PCB_100H
SW48: Z; CHERRY_PCB_100H
SW49: SHIFT; CHERRY_PCB_225H
SW50: CTRL; CHERRY_PCB_125H
SW51: GRAPH; CHERRY_PCB_125H
SW52: CAPS_LOCK; CHERRY_PCB_175H
SW53: CODE/KANA; CHERRY_PCB_125H
SW54: F1/F6; CHERRY_PCB_100H
SW55: F2/F7; CHERRY_PCB_100H
SW56: F3/F8; CHERRY_PCB_100H
SW57: F4/F9; CHERRY_PCB_100H
SW58: F5/F10; CHERRY_PCB_100H
SW59: ESC; CHERRY_PCB_100H
SW60: TAB; CHERRY_PCB_150H
SW61: STOP; CHERRY_PCB_100H
SW62: BACK_SPACE; CHERRY_PCB_200H
SW63: SELECT; CHERRY_PCB_125H
SW64: RETURN; CHERRY_PCB_225H
SW65: SPACE; CHERRY_PCB_625H
SW66: HOME/CLS; CHERRY_PCB_100H
SW67: INSERT; CHERRY_PCB_100H
SW68: DELETE; CHERRY_PCB_100H
SW69: LEFT; CHERRY_PCB_100H
SW70: UP; CHERRY_PCB_100H
SW71: DOWN; CHERRY_PCB_100H
SW72: RIGHT; CHERRY_PCB_100H
SW73: SHIFT; CHERRY_PCB_275H
U1: 74LS145; IC_DIP16_300
U2: 74LS07; IC_DIP14_300

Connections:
/CAPS_LED: J1.12, U2.13
/CAPS_LED_BUFFERED: D2.1 (K), U2.12
/CODE: D6.2 (A), SW53.1
/COLUMN0: RN1.3 (R2), SW1.2, SW9.2, SW17.2, SW25.2, SW33.2, SW41.2, SW49.2, SW57.2, SW65.2, SW73.2, U2.5
/COLUMN0_BUF: J1.1, U2.6
/COLUMN1: J1.3, SW2.2, SW10.2, SW18.2, SW26.2, SW34.2, SW42.2, SW50.2, SW58.2, SW66.2
/COLUMN2: RN1.4 (R3), SW3.2, SW11.2, SW19.2, SW27.2, SW35.2, SW43.2, SW51.2, SW59.2, SW67.2, U2.3
/COLUMN2_BUF: J1.5, U2.4
/COLUMN3: J1.7, SW4.2, SW12.2, SW20.2, SW28.2, SW36.2, SW44.2, SW52.2, SW60.2, SW68.2
/COLUMN4: RN1.5 (R4), SW5.2, SW13.2, SW21.2, SW29.2, SW37.2, SW45.2, SW53.2, SW61.2, SW69.2, U2.1
/COLUMN4_BUF: J1.9, U2.2
/COLUMN5: J1.11, SW6.2, SW14.2, SW22.2, SW30.2, SW38.2, SW46.2, SW54.2, SW62.2, SW70.2
/COLUMN6: J1.13, SW7.2, SW15.2, SW23.2, SW31.2, SW39.2, SW47.2, SW55.2, SW63.2, SW71.2
/COLUMN7: J1.15, SW8.2, SW16.2, SW24.2, SW32.2, SW40.2, SW48.2, SW56.2, SW64.2, SW72.2
/D1+: D1.2 (A), R1.2
/D2+: D2.2 (A), R2.2
/D3+: D3.2 (A), R3.2
/GRAPH: D5.2 (A), SW51.1
/KANA_LED: J1.14, U2.11
/KANA_LED_BUFFERED: D3.1 (K), U2.10
/ROW0: SW1.1, SW2.1, SW3.1, SW4.1, SW5.1, SW6.1, SW7.1, SW8.1, U1.1 (Q0)
/ROW1: SW9.1, SW10.1, SW11.1, SW12.1, SW13.1, SW14.1, SW15.1, SW16.1, U1.2 (Q1)
/ROW2: SW17.1, SW18.1, SW19.1, SW20.1, SW21.1, SW22.1, SW23.1, SW24.1, U1.3 (Q2)
/ROW3: SW25.1, SW26.1, SW27.1, SW28.1, SW29.1, SW30.1, SW31.1, SW32.1, U1.4 (Q3)
/ROW4: SW33.1, SW34.1, SW35.1, SW36.1, SW37.1, SW38.1, SW39.1, SW40.1, U1.5 (Q4)
/ROW5: SW41.1, SW42.1, SW43.1, SW44.1, SW45.1, SW46.1, SW47.1, SW48.1, U1.6 (Q5)
/ROW6: D4.1 (K), D5.1 (K), D6.1 (K), SW50.1, SW52.1, SW54.1, SW55.1, SW56.1, U2.8
/ROW6_UNBUF: RN1.2 (R1), U1.7 (Q6), U2.9
/ROW7: SW57.1, SW58.1, SW59.1, SW60.1, SW61.1, SW62.1, SW63.1, SW64.1, U1.9 (Q7)
/ROW8: SW65.1, SW66.1, SW67.1, SW68.1, SW69.1, SW70.1, SW71.1, SW72.1, U1.10 (Q8)
/ROW_A: J1.4, U1.15 (P0)
/ROW_B: J1.6, U1.14 (P1)
/ROW_C: J1.8, U1.13 (P2)
/ROW_D: J1.10, U1.12 (P3)
/SHIFT: D4.2 (A), SW49.1, SW73.1
GND: C1.2, C2.2, C3.2, D1.1 (K), HOLE1.1, HOLE2.1, HOLE3.1, HOLE4.1, HOLE5.1, HOLE6.1, HOLE7.1, J1.16, U1.8 (GND), U2.7 (GND)
VCC: C1.1, C2.1, C3.1, J1.2, R1.1, R2.1, R3.1, RN1.1 (common), U1.16 (VCC), U2.14 (VCC)

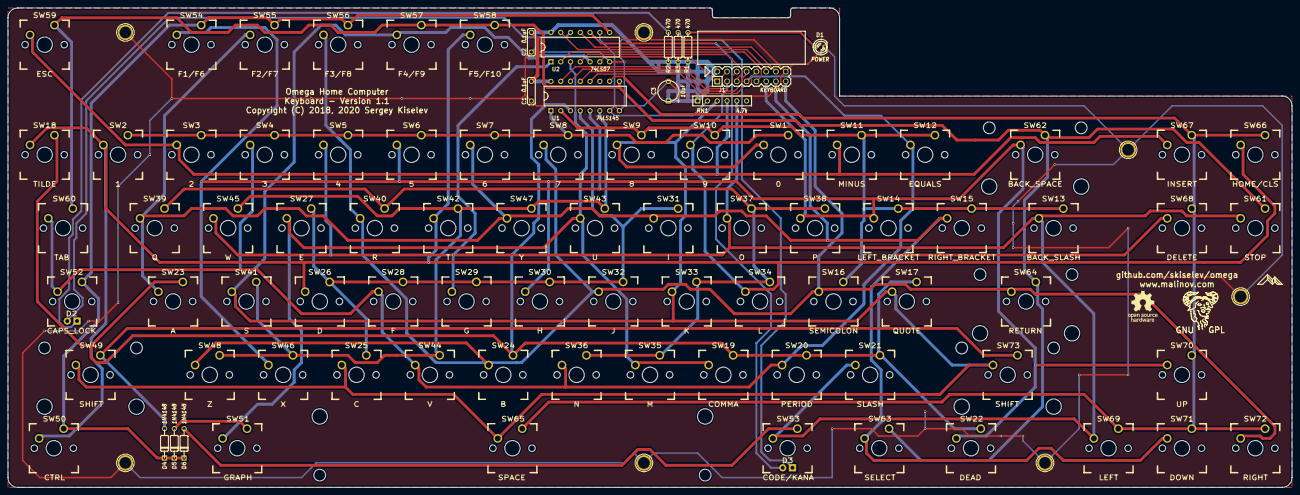
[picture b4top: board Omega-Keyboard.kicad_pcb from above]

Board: 2 copper layers, 333.4 x 124.5 mm, 96 parts (0 on the bottom side), 37 nets.

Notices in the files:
reference-projects/CERBERUS_2080/Kicad-version/CERBERUS_2080/CERBERUS_2080.kicad_pcb:
All rights reserved
Copyright 2020-2021
Provided as-is, under license
Copyright 2021 by
reference-projects/omega-master/Hardware/Keyboard/KiCad/Omega-Keyboard.kicad_pcb:
Copyright (C) 2018, 2020 Sergey Kiselev
